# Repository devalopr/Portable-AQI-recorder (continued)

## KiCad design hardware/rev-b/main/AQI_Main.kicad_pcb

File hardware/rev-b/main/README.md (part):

# AQI main board — Rev B

Open `AQI_Main.kicad_pro` in KiCad 10. This board mates with the IP5310 battery board, which now lives in its own private repo, [18650-USB-C-UPS](https://github.com/devalopr/18650-USB-C-UPS). It started from the routed Rev A main board, whose design is kept in `review/rev-a-baseline/` as the input to `main_revb_design.py`; the rest of Rev A is in git history.

**47 × 76 mm, two layers, 1.6 mm.** This is 4 mm shorter and 3 mm wider than Rev A, and two layers instead of four. The previous 4-layer, 80 mm version is kept in `review/rev-b-4layer-80mm/` (board, `design.json` and its cost).

Changes in the 2-layer, 47 × 76 mm re-layout:

- **Wider, with mounting lips.** The board grew 1.5 mm on each long side, from 44 to 47 mm, for routing room. Board coordinates keep the Rev A origin, so the board now spans x = −1.5 to 45.5 mm. The outer 1 mm on each side (x = −1.5 to −0.5 and 44.5 to 45.5 mm) is a lip for clamping the board in the case. It carries only the ground pour: no tracks or vias. SW4 moved out 1.5 mm with the edge.

- **Shorter bottom.** Everything below the buttons moved up 4 mm and the bottom edge was cut to match:
  - the ESP32 module, which keeps its antenna at the edge, and its supply caps;
  - USB-C and D1;
  - the J2/J8 headers.

  The limit is USB-C: its shield legs pass through the board and must stay clear of the OK button's pads.
- **CO₂ on top.** The CO₂ island is now at the top of the right column (y = 21–35 mm, under J5), above SEN5x and SEN6x. It is fed through its bottom-right tab instead of the middle tab (see Layout). Set `ISLAND_DY = 0` in `main_revb_2layer.py` to go back to the island at the bottom of the column.
- **Sensor connectors.** J3 (SEN5x, y = 37–49 mm) and J4 (SEN6x, y = 49.8–59.4 mm) sit below the island, 6 mm in from the original right edge. Their mouths face the edge from x = 37.5 mm, leaving 8 mm on the board for the GH plug and for the cable to bend down before it reaches the case.
- **E-paper through an adapter.** The on-board e-paper boost circuit and its 24-pin FPC connector are gone. An unfitted 8-pin header J6 takes their place (see below).
- **Two layers.** The front copper, where only the buttons sit, carries ground plus as few signals as possible. A few critical nets are laid first as fixed routes (see Layout), and the rest are routed around them.

## Front: display and buttons

The front carries only the display and the three buttons. Everything else, including USB-C, is on the back.

- **Display.** A 2.4-inch 240 × 320 ST7789 panel with a 10-way, 1.0 mm-pitch flex.
  - **Size:** 42.72 × 60.26 × 2.5 mm, with a 36.72 × 48.96 mm active area (common datasheet values; you measured about 42.5 × 60 × 2.5 mm).
  - **Position:** centred in the Rev A display envelope, which spans x = 0.64–43.36 mm, y = 1.5–62.46 mm (board origin top-left, seen from the front). The panel itself spans y = 1.85–62.11 mm.
  - **Height:** it sits on 0.2 mm tape, so its front face is 2.7 mm above the board.
  - **Flex:** exits at the top, wraps over the top edge (about 1.5 mm past it) and runs into J5 on the back. The active area therefore sits toward the buttons, and firmware rotates the image.
  - **In the files:** the board-only footprint DS1 carries the panel's 3D model and outline. It isn't in the BOM or the placement file. The envelope is also drawn on Dwgs.User, labelled "TFT DISPLAY BODY (FRONT)".
  - The active-area offsets (3.0 mm at the sides, 3.2 mm at the far end, 8.1 mm at the flex end) and the flex path are typical values, not from your panel's drawing. Check them against the part you buy.
  - Nothing is placed on the front under the panel.
- **Buttons.** SW1 LEFT, SW2 OK and SW3 RIGHT sit in one row directly below the display:
  - centres at x = 9, 22 and 35 mm, y = 66.25 mm;
  - an even 13 mm pitch, centred on the board and the display (x = 22);
  - XKB TS-1187A: 5.1 × 5.1 mm body, 1.5 mm tall;
  - bodies at y = 63.7–68.8 mm, about 1.2 mm below the display edge.

  The switch tops (1.5 mm) are 1.2 mm below the display face (2.7 mm), so the enclosure needs button caps or plungers that reach the front face. The silkscreen labels L / OK / R are under each button.
- **3D models.** They are all in `lib/3d/` and the footprints point at them through `${KIPRJMOD}`; see `lib/3d/README.md`.
  - USB-C uses the LCSC catalogue model shared with the battery board.
  - KiCad 10 has no models for the TS-1187A buttons or the MSK12C02 power switch. They use simplified envelopes built from the footprint and datasheet dimensions, with their build123d sources alongside.

## Cost

About **$4.63 (₹444) per board at 1000** boards:

| At 1000 boards | Per board |
|---|---:|
| Parts | $4.01 |
| 2-layer fabrication, 47 × 76 mm | $0.13 (4-layer, 80 mm was $0.30) |
| JLC assembly | $0.49 |

Five prototypes cost about $31 each, mostly JLC's per-order assembly setup; the bare 2-layer boards are about $2 for five. Details, assumptions and exclusions are in [review/COST.md](review/COST.md). Only the SCD41 (U8) and the J6/J8 headers are unfitted; the CO₂ supply (LDO U7 with C15, C16 and C42, about $0.24) is assembled so the sensor can be soldered in later on its own. The same design with its original parts was about $10.7 (₹1030) at 1000.

## E-paper option (J6, unfitted)

The stationary version can use an e-paper display instead of the TFT. The panel from the Rev A brief, Good Display GDEY037T03, is a bare panel: it needs a boost circuit (about ±15 V gate and source rails) on whatever board its 24-pin flex plugs into. Rev A put that circuit on this board as an unfitted option: 22 parts plus the FPC connector. Rev B leaves the boost circuit to an external adapter instead:

- **Adapter.** Good Display's DESPI-C02 takes the panel's 24-pin flex and makes the rails. The same adapter fits most of Good Display's 24-pin SPI panels, so the main board isn't tied to one panel. A module with its own driver board (for example Waveshare's) also works.
- **J6.** A 1 × 8, 2.54 mm SMD pin header on the back at the top-left edge (pads staggered at x = 3.35 and 6.66 mm, y = 1.5–19.3 mm). Like J8, it is unfitted (DNP) by default and is left out of the JLC BOM and placement files; solder it by hand for an e-paper build. It sits near the board edge, clear of J5, so there's room for the iron. It's surface-mount so no through-hole pads sit under the TFT in the default build. Pin 1 is at the top; the pin names are on the back silkscreen, on the side toward J5.

| J6 pin | DESPI-C02 pin | Signal | ESP32 |
|---:|---|---|---|
| 1 | BUSY | EPD_BUSY | GPIO20 |
| 2 | RES | DISP_RST | GPIO7 |
| 3 | D/C | DISP_DC | GPIO10 |
| 4 | CS | DISP_CS | GPIO4 |
| 5 | SCK | DISP_SCK | GPIO5 |
| 6 | SDI | DISP_MOSI | GPIO6 |
| 7 | GND | GND | |
| 8 | 3.3V | +3V2 (3.19 V) | |

A straight 8-way female-to-female cable maps J6 pin n to DESPI-C02 pin n. Waveshare modules use the same signals in reverse order (VCC, GND, DIN, CLK, CS, DC, RST, BUSY).

The display SPI, CS, DC and reset are shared with the TFT, so **fit one display only**. The adapter's supply comes from the +3V2 rail; e-paper refresh current is small. Firmware still has to supply a driver for the chosen panel: ESPHome has no working UC8253 (GDEY037T03) driver yet (see the Rev A brief), so either pick a panel ESPHome supports or bench-test a custom component.

## Interface to the battery board

- **USB-C J1 is the only power and data input.** It is the same SHOU HAN TYPE-C 16P L6.5 (LCSC C49287211) as the battery board's J1 and J7, using that board's footprint (checked against the maker's drawing) and 3D model. It is on the back, at x = 26.7 mm on the bottom edge (y = 76), with its mouth flush with the edge. That is about 11 mm nearer the centre than in Rev A. Plug it into the battery board's USB-C output J7, which carries 5 V plus USB data passed through from the battery board's input port. It can also plug straight into a computer or adapter.
- **J2: straight 2.54 mm Dupont header for battery %** (hanxia HX PZ2.54-1x2P ZZ, LCSC C32713268), back side, bottom-right, pin 1 at (33.85, 72.1) mm. The pins stand up from the back, toward the battery board; nothing overhangs the edge. Pin 1 = GND, pin 2 = BAT_PWM, the same order as battery J9, so a straight female-female jumper works. R33 (10 kΩ) pulls BAT_PWM up to +3V2; R34 (1 kΩ) feeds GPIO21. Encoding and receiver: `../firmware/telemetry/README.md`.
- **J8: straight Dupont header for external 5 V, unpopulated** (same part), next to J2 (pin 1 at x = 39.95 mm). Pin 1 = GND, pin 2 = 5 V in. D2 (B5819W Schottky, fitted) feeds +5V_SYS, the same point as USB VBUS. The switch and regulators work as normal, and the diode stops the board back-feeding the external supply. A supply above USB VBUS + 0.3 V can back-feed a connected USB host, so don't plug USB into a computer while an external 5 V is attached.
- Removed with the 10-way JST GH link:
  - the TS3USB30E USB data mux;
  - the TPS2116 power mux;
  - their FETs and resistors;
  - C4, C5, C6 and R24.

  No I2C runs to the battery board any more.

## Cost-down changes (same functions)

| Part | Rev A | Rev B |
|---|---|---|
| U5, U6 bucks | TPS62160 (MSOP-8) | Silergy SY8089A1AAC (SOT-23-5). The datasheet's optional feed-forward caps are omitted. |
| Buttons | MCP23008 I2C expander + C&K KMR2 | Straight to GPIOs; XKB TS-1187A 5.1 mm switches. U9, C17, R23 and R25 removed. |
| Backlight | STCS05A current sink (not stocked at JLC) | AO3400A low-side switch Q1 with R28 = 33 Ω 1206 (~55 mA at Vf 3.1 V). Still PWM-dimmable on GPIO3; the current is set by the resistor, not regulated. |
| Power switch | C&K JS102011SAQN | Shou Han MSK12C02; its actuator sticks out about 1.1 mm past the right edge. |
| USB-C | GCT USB4105 | SHOU HAN TYPE-C 16P L6.5, the battery board's part ($0.047 at 1000, against $0.103 for the HRO TYPE-C-31-M-12 it replaced) |
| Sensor connectors J3, J4 | JST GH | XYECO GH-compatible clones, same footprint |
| ESD, MCU | ST USBLC6-2SC6, ESP32-C3-MINI-1-H4 | Tech Public USBLC6-2SC6, ESP32-C3-MINI-1-H4X (same footprint) |

Every fitted part has an LCSC code in the schematic. `review/jlc-bom.csv` and `review/jlc-cpl.csv` are ready for JLCPCB assembly. The board is double-sided: the three buttons are on the front and everything else is on the back.

The TFT connector (TE 1-84953-0, $0.44) stays: no cheap top-contact 1.0 mm 10-pin FPC connector is stocked, and the display needs top contact.

## Firmware pin map

The firmware in [firmware/](../../../firmware/README.md) uses this map. The board is programmed and logs over J1 (native USB); see that README.

| ESP32 GPIO | Function |
|---|---|
| 10 | Display DC |
| 4 | Display CS |
| 5 | Display SCK |
| 6 | Display MOSI |
| 7 | Display RST |
| 8 | LEFT button, active low, R3 pull-up |
| 9 | OK button, active low, R2 pull-up. Hold OK while resetting to enter the ROM bootloader. |
| 2 | RIGHT button, active low, R4 pull-up |
| 21 | BAT_PWM input through R34. Use native USB for logs; do not enable UART TX on GPIO21. |
| 3 | Backlight PWM, now driving a MOSFET gate (R27 pull-down) |
| 0 | I²C SDA (SEN5x at 0x69, SEN6x at 0x6B, SCD4x at 0x62) |
| 1 | I²C SCL |
| 20 | E-paper BUSY (J6 pin 1), input; also the ROM UART RX |
| 18, 19 | Native USB D−, D+ (to J1 through R7/R8 and D1) |

GPIO2, 8 and 9 are boot-strap pins. Don't hold LEFT or RIGHT while resetting; OK held at reset is the intended download mode. The buttons need a pull-up at reset, which R2–R4 provide; there's no I2C expander any more.

The 2-layer layout changed the display pins so they leave the module in the TFT connector's order (DC, CS, SCK, MOSI, RST); this lets the bus run without crossings:

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
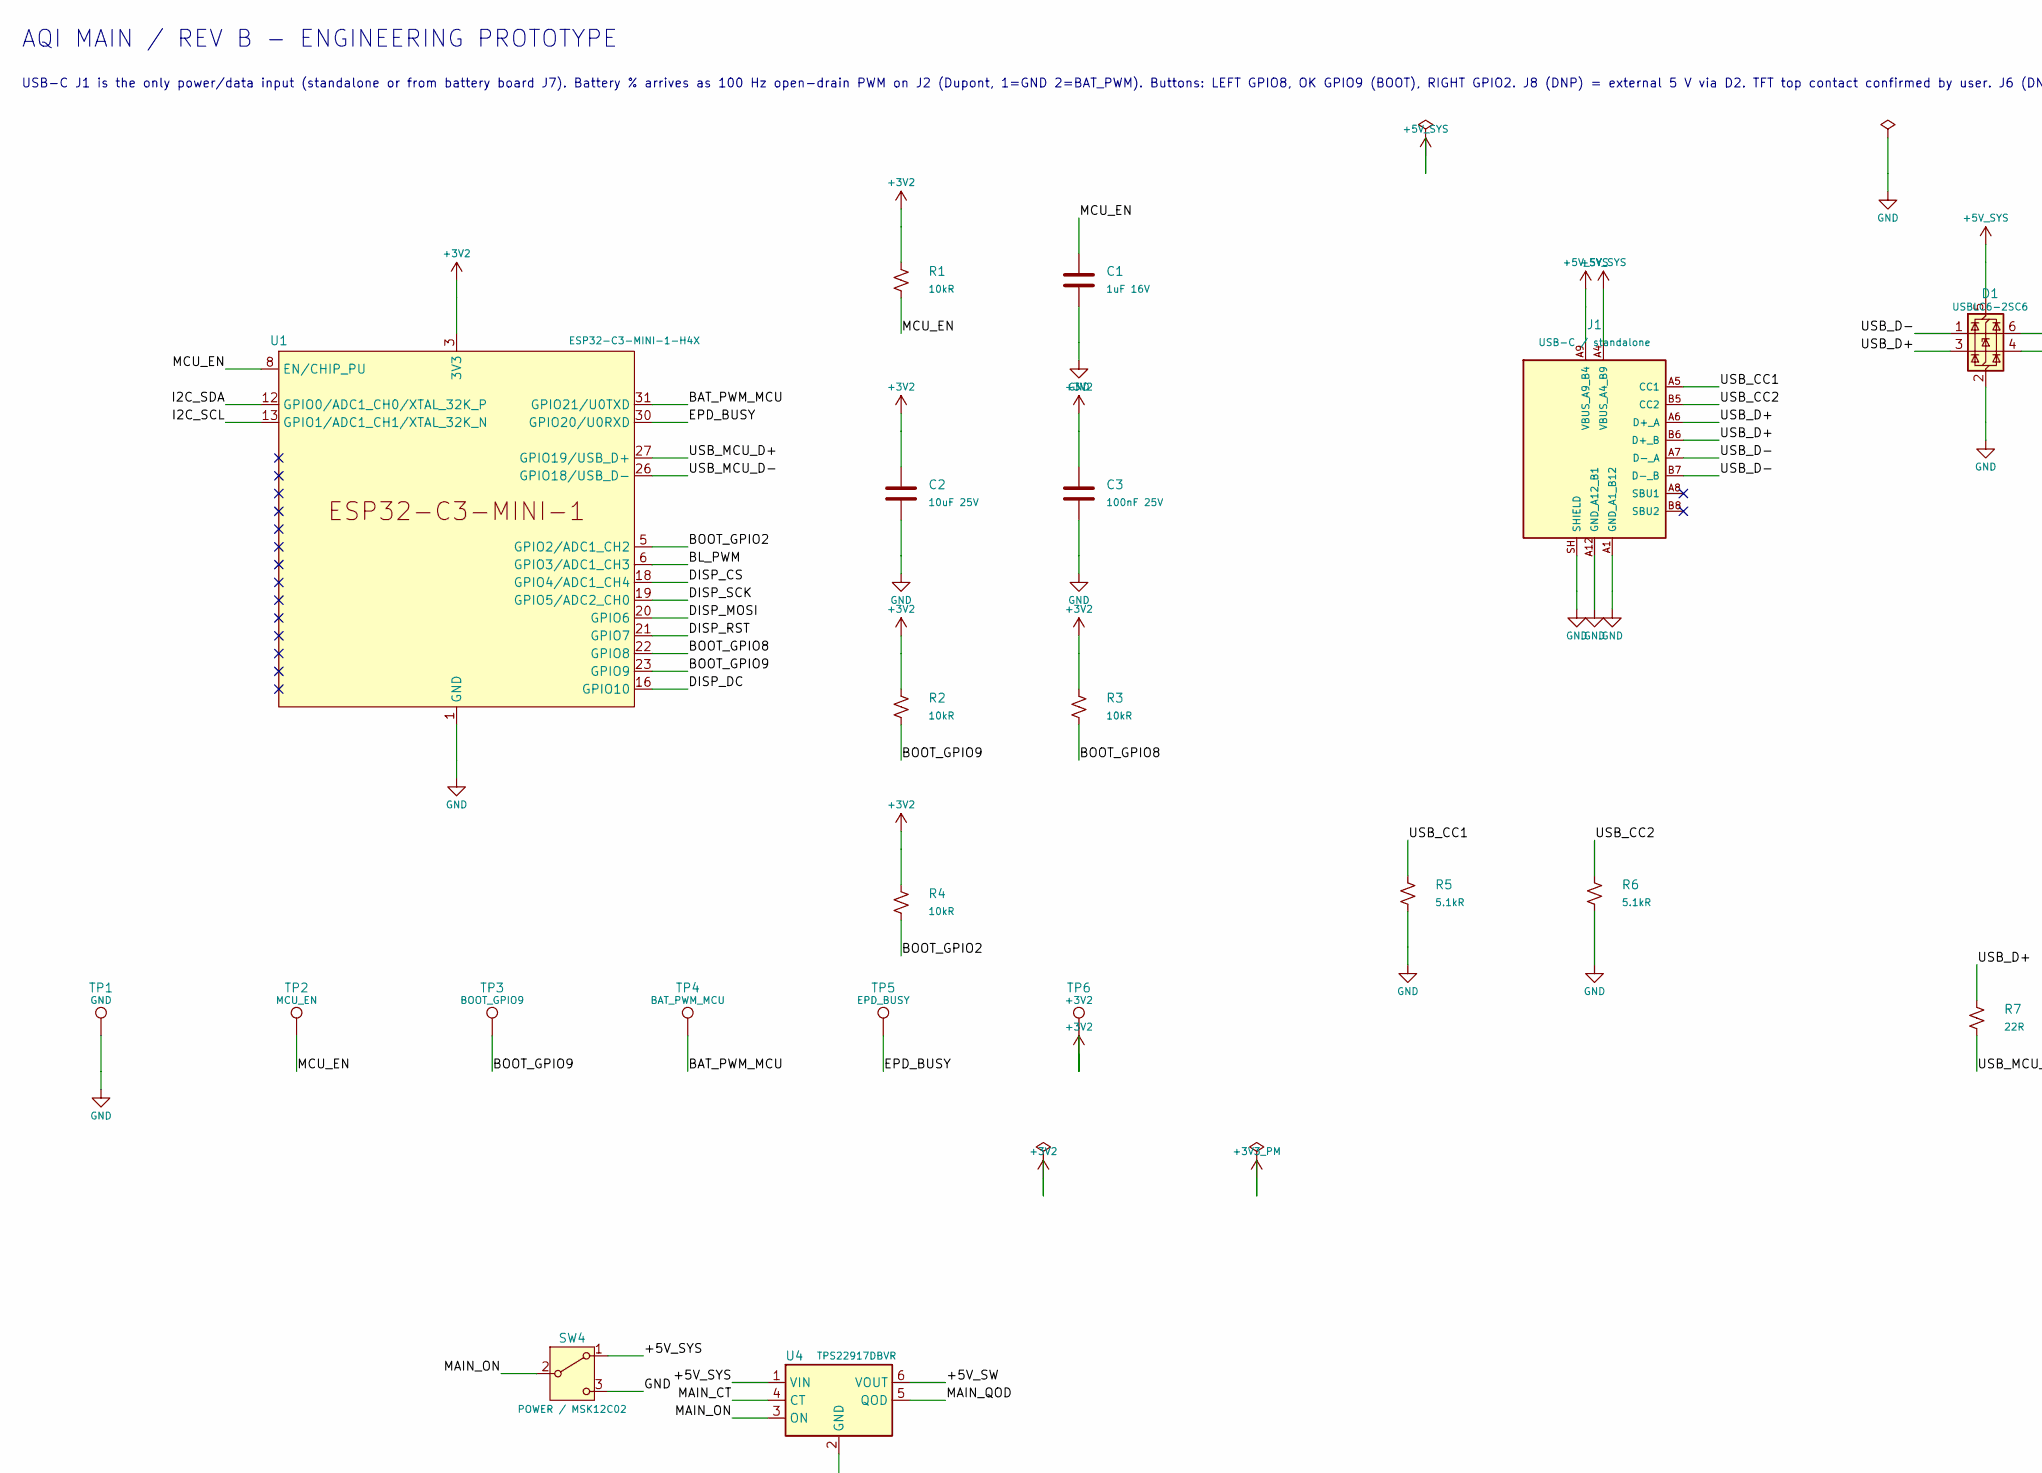
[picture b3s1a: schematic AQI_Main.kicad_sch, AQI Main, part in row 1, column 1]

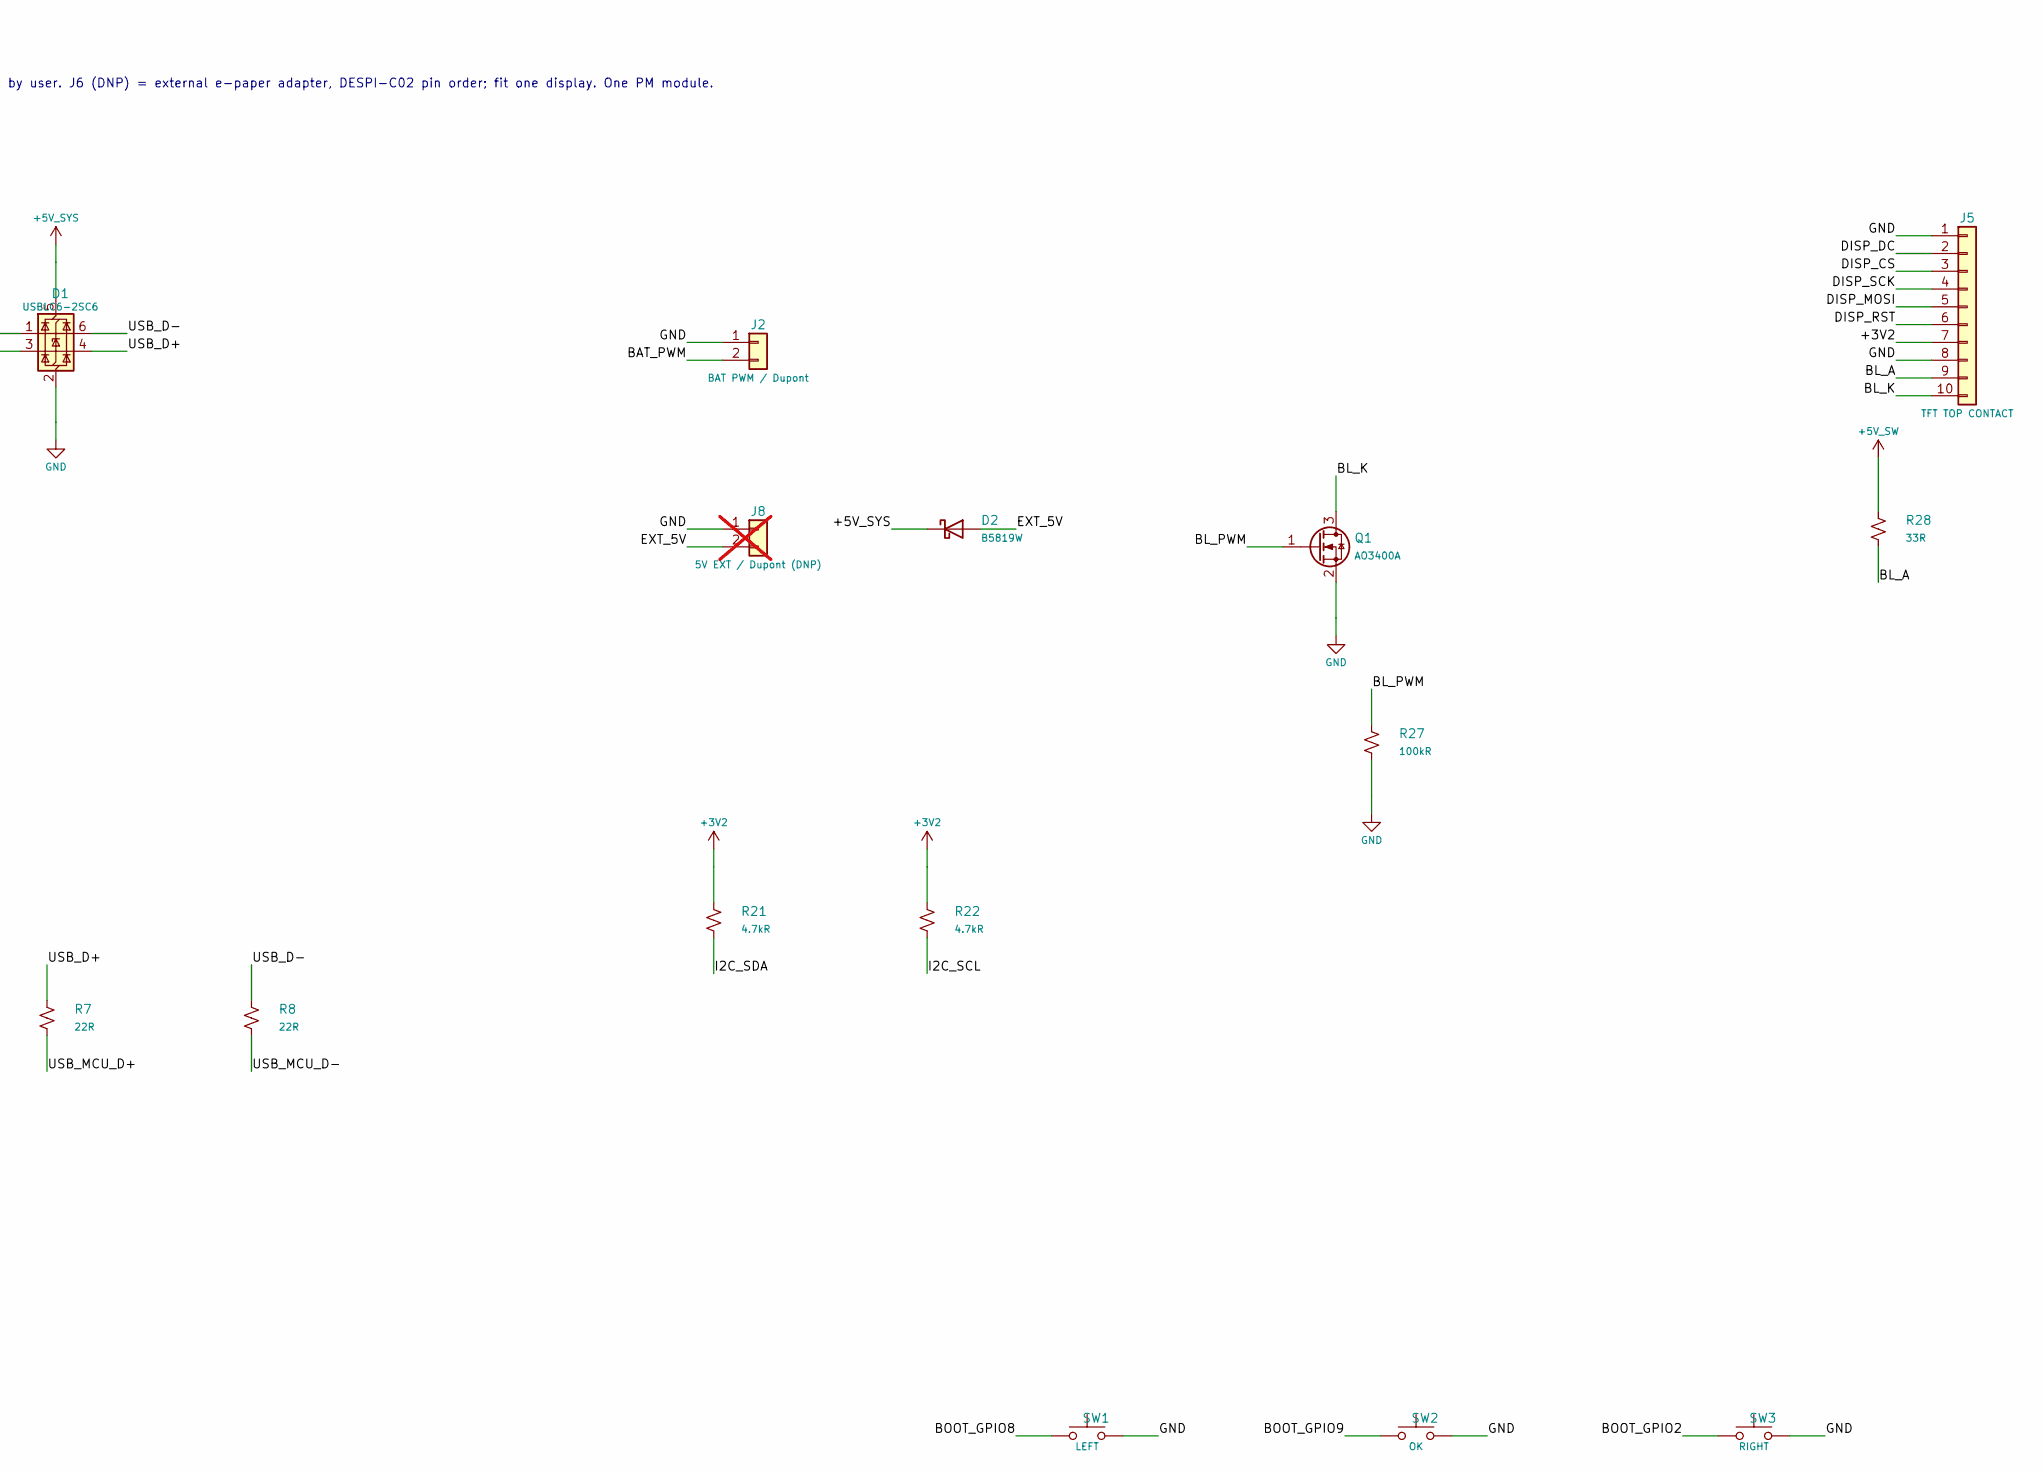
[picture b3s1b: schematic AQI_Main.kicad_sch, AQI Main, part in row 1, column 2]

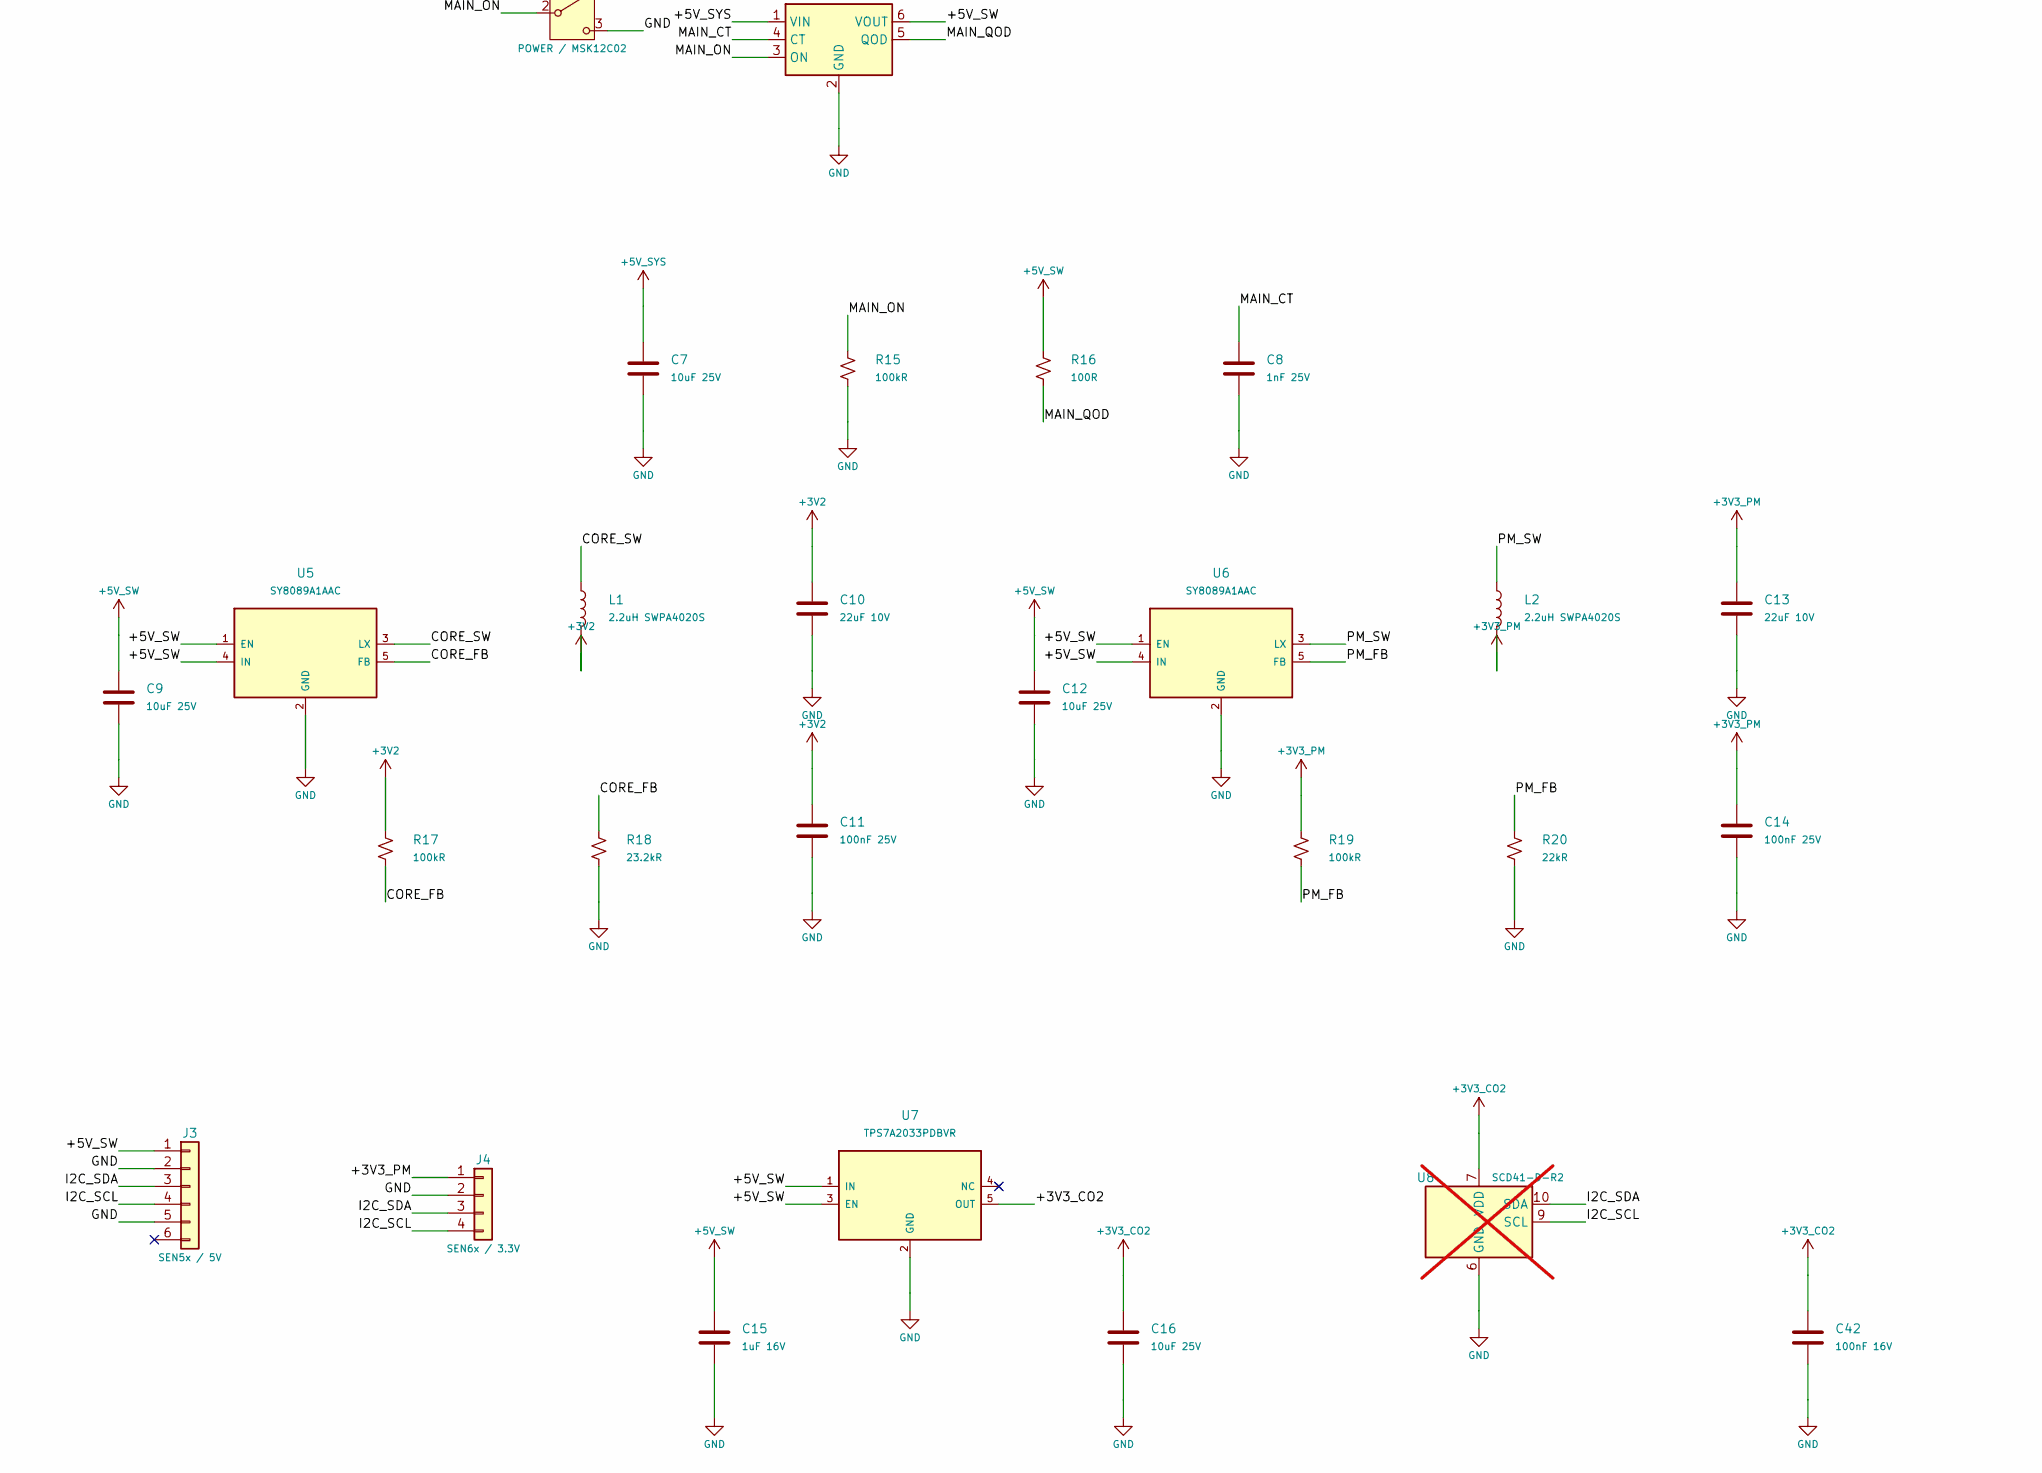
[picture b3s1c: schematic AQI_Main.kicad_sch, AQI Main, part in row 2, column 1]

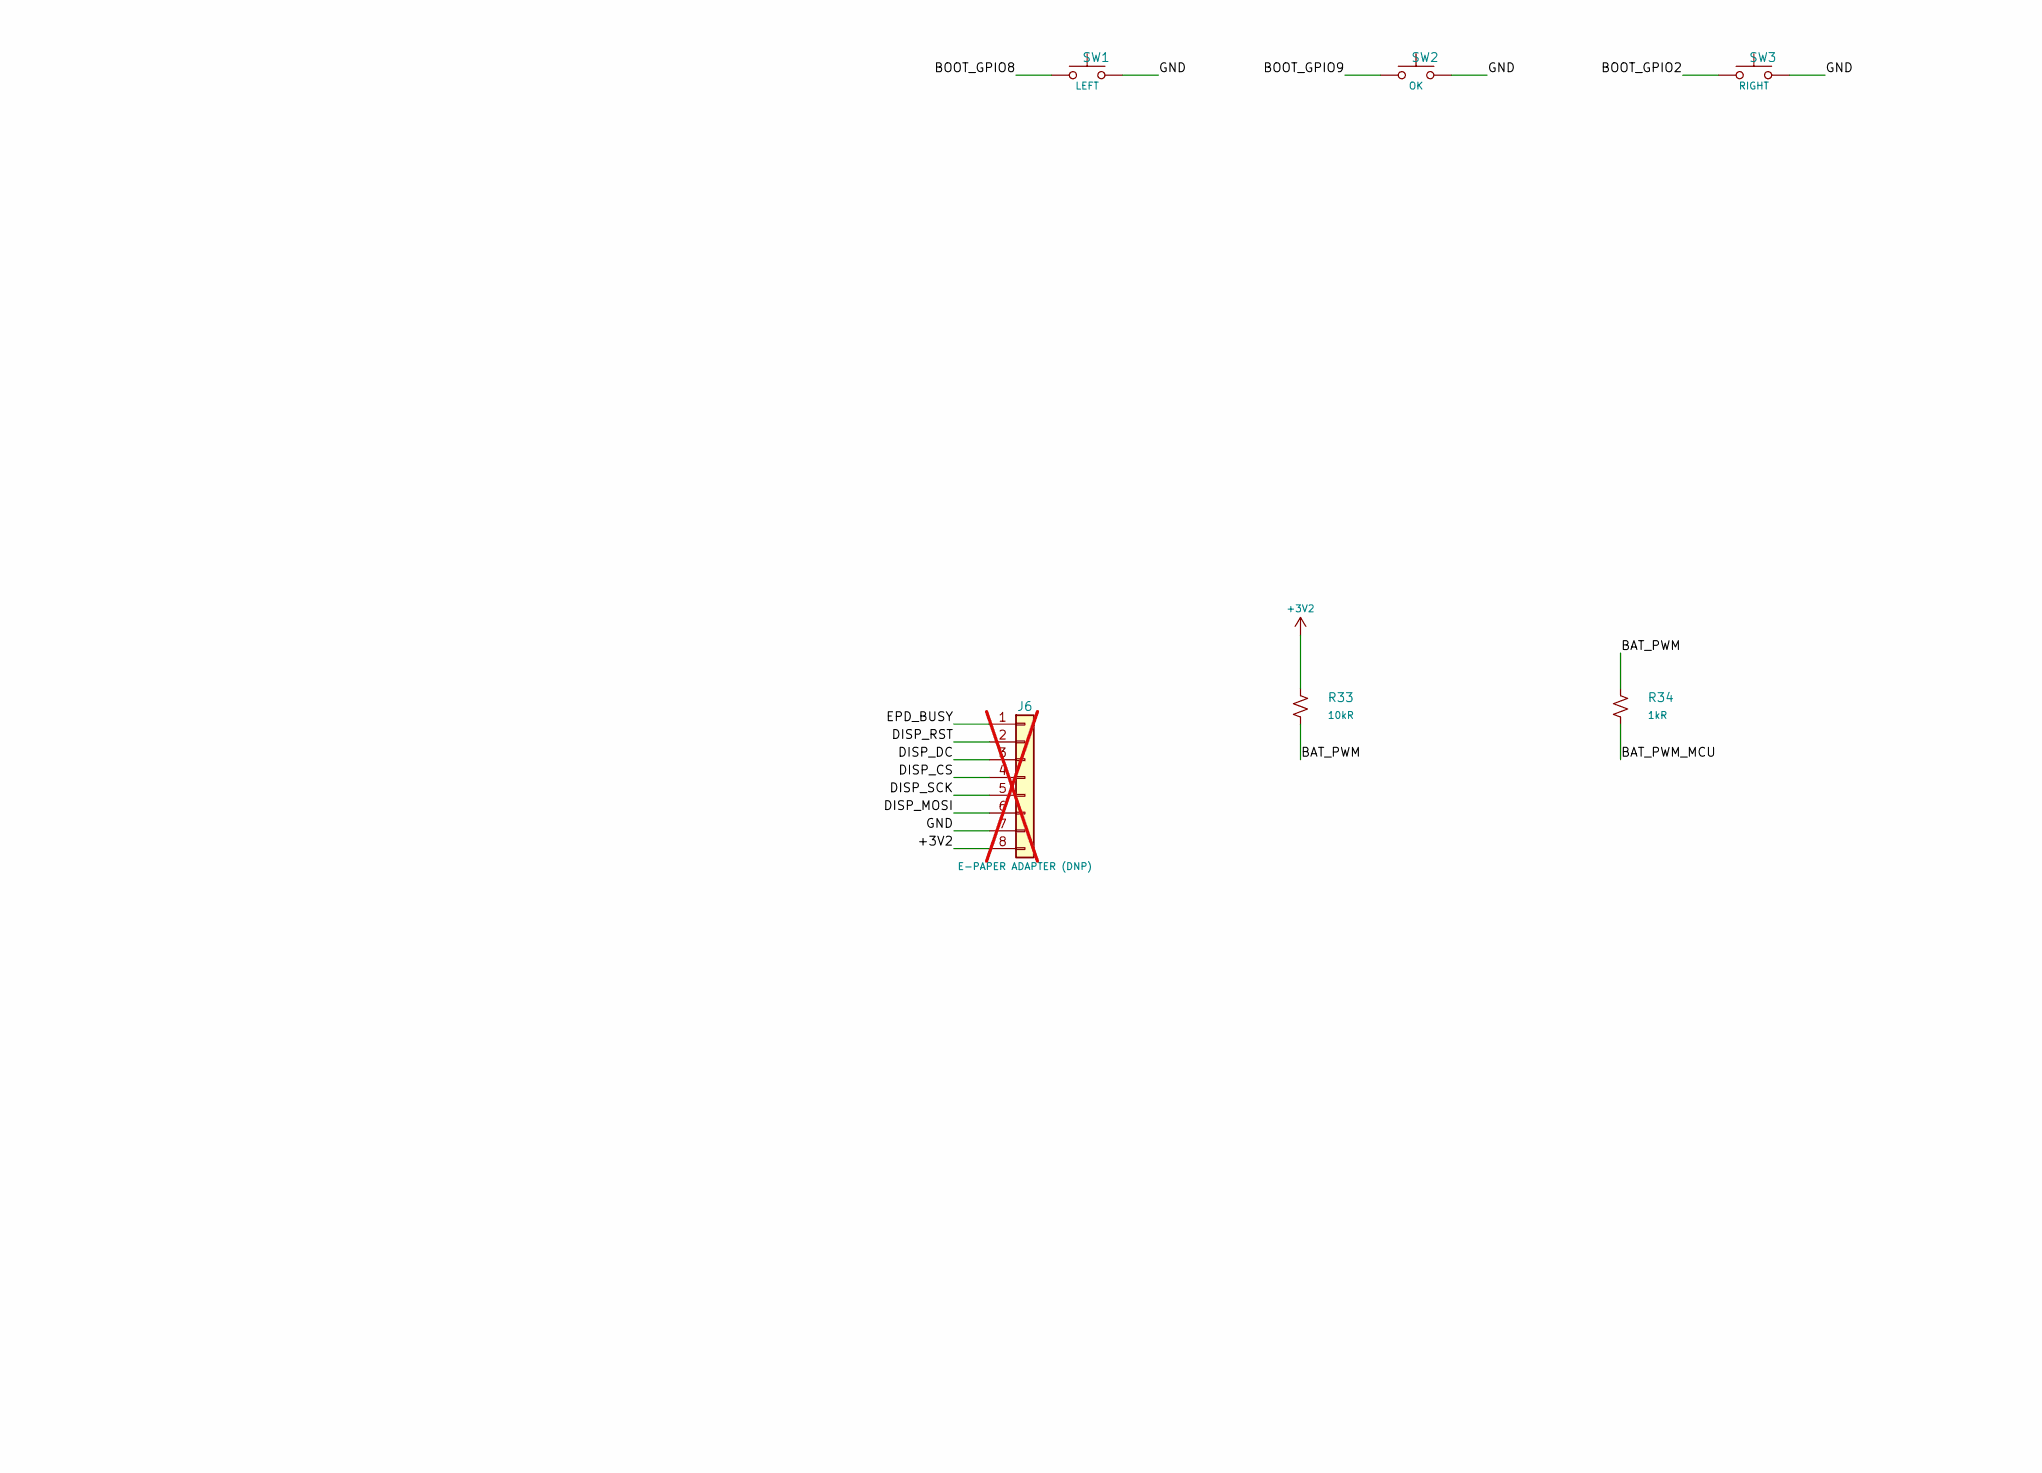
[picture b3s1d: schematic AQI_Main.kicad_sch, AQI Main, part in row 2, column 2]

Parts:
C1, C15: 1uF 16V; C_0603_1608Metric; LCSC C15849
C2, C7, C9, C12, C16: 10uF 25V; C_0805_2012Metric; LCSC C15850
C3, C11, C14: 100nF 25V; C_0603_1608Metric; LCSC C14663
C8: 1nF 25V; C_0603_1608Metric; LCSC C1588
C10, C13: 22uF 10V; C_0805_2012Metric; LCSC C45783
C42: 100nF 16V; C_0402_1005Metric; LCSC C1525
D1: USBLC6-2SC6; SOT-23-6; MPN USBLC6-2SC6; LCSC C2827654
D2: B5819W; D_SOD-123; MPN B5819W SL; LCSC C8598
J1: USB-C / standalone; USB-C-SMD_TYPE-C-16P-L6.5; MPN TYPE-C 16P L6.5; LCSC C49287211
J2: BAT PWM / Dupont; PinHeader_1x02_P2.54mm_Vertical; MPN HX PZ2.54-1x2P ZZ; LCSC C32713268
J3: SEN5x / 5V; JST_GH_SM06B-GHS-TB_1x06-1MP_P1.25mm_Horizontal; MPN XY-SM06B-GHS-TB; LCSC C51940119
J4: SEN6x / 3.3V; JST_GH_SM04B-GHS-TB_1x04-1MP_P1.25mm_Horizontal; MPN XY-SM04B-GHS-TB; LCSC C51940118
J5: TFT TOP CONTACT; TE_1-84953-0_1x10-1MP_P1.0mm_Horizontal; MPN 1-84953-0; LCSC C3168738
J6: E-PAPER ADAPTER (DNP); PinHeader_1x08_P2.54mm_Vertical_SMD_Pin1Left; MPN 2.54mm 1x08 SMD pin header; not fitted
J8: 5V EXT / Dupont (DNP); PinHeader_1x02_P2.54mm_Vertical; MPN HX PZ2.54-1x2P ZZ; LCSC C32713268; not fitted
L1, L2: 2.2uH SWPA4020S; L_Sunlord_SWPA4020S; MPN SWPA4020S2R2MT; LCSC C83423
Q1: AO3400A; SOT-23; MPN AO3400A; LCSC C20917
R1, R2, R3, R4, R33: 10kR; R_0603_1608Metric; LCSC C25804
R5, R6: 5.1kR; R_0603_1608Metric; LCSC C23186
R7, R8: 22R; R_0603_1608Metric; LCSC C23345
R15, R17, R19, R27: 100kR; R_0603_1608Metric; LCSC C25803
R16: 100R; R_0603_1608Metric; LCSC C22775
R18: 23.2kR; R_0603_1608Metric; LCSC C49656146
R20: 22kR; R_0603_1608Metric; LCSC C31850
R21, R22: 4.7kR; R_0603_1608Metric; LCSC C23162
R28: 33R; R_1206_3216Metric; LCSC C25375
R34: 1kR; R_0603_1608Metric; LCSC C21190
SW1: LEFT; SW_Push_1P1T_XKB_TS-1187A; MPN TS-1187A-B-A-B; LCSC C318884
SW2: OK; SW_Push_1P1T_XKB_TS-1187A; MPN TS-1187A-B-A-B; LCSC C318884
SW3: RIGHT; SW_Push_1P1T_XKB_TS-1187A; MPN TS-1187A-B-A-B; LCSC C318884
SW4: POWER / MSK12C02; SW_SPDT_Shouhan_MSK12C02; MPN MSK12C02; LCSC C431540
TP1: GND; TestPoint_Pad_D1.0mm
TP2: MCU_EN; TestPoint_Pad_D1.0mm
TP3: BOOT_GPIO9; TestPoint_Pad_D1.0mm
TP4: BAT_PWM_MCU; TestPoint_Pad_D1.0mm
TP5: EPD_BUSY; TestPoint_Pad_D1.0mm
TP6: +3V2; TestPoint_Pad_D1.0mm
U1: ESP32-C3-MINI-1-H4X; ESP32-C3-MINI-1; MPN ESP32-C3-MINI-1-H4X; LCSC C41349510
U4: TPS22917DBVR; SOT-23-6; MPN TPS22917DBVR; LCSC C2681320
U5, U6: SY8089A1AAC; SOT-23-5; MPN SY8089A1AAC; LCSC C479074
U7: TPS7A2033PDBVR; SOT-23-5; MPN TPS7A2033PDBVR; LCSC C2862740
U8: SCD41-D-R2; Sensirion_SCD4x-1EP_10.1x10.1mm_P1.25mm_EP4.8x4.8mm; MPN SCD41-D-R2; not fitted

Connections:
+3V2: C2.1, C3.1, C10.1, C11.1, J5.7, J6.8, L1.2, R1.1, R2.1, R3.1, R4.1, R17.1, R21.1, R22.1, R33.1, TP6.1, U1.3 (3V3)
+3V3_CO2: C16.1, C42.1, U7.5 (OUT), U8.7 (VDD), U8.19 (VDD)
+3V3_PM: C13.1, C14.1, J4.1, L2.2, R19.1
+5V_SW: C9.1, C12.1, C15.1, J3.1, R16.1, R28.1, U4.6 (VOUT), U5.1 (EN), U5.4 (IN), U6.1 (EN), U6.4 (IN), U7.1 (IN), U7.3 (EN)
+5V_SYS: C7.1, D1.5 (VBUS), D2.1 (K), J1.A4 (VBUS_A4_B9), J1.A9 (VBUS_A9_B4), SW4.1 (A), U4.1 (VIN)
/BAT_PWM: J2.2, R33.2, R34.1
/BAT_PWM_MCU: R34.2, TP4.1, U1.31 (GPIO21/U0TXD)
/BL_A: J5.9, R28.2
/BL_K: J5.10, Q1.3 (D)
/BL_PWM: Q1.1 (G), R27.1, U1.6 (GPIO3/ADC1_CH3)
/BOOT_GPIO2: R4.2, SW3.1, U1.5 (GPIO2/ADC1_CH2)
/BOOT_GPIO8: R3.2, SW1.1, U1.22 (GPIO8)
/BOOT_GPIO9: R2.2, SW2.1, TP3.1, U1.23 (GPIO9)
/CORE_FB: R17.2, R18.1, U5.5 (FB)
/CORE_SW: L1.1, U5.3 (LX)
/DISP_CS: J5.3, J6.4, U1.18 (GPIO4/ADC1_CH4)
/DISP_DC: J5.2, J6.3, U1.16 (GPIO10)
/DISP_MOSI: J5.5, J6.6, U1.20 (GPIO6)
/DISP_RST: J5.6, J6.2, U1.21 (GPIO7)
/DISP_SCK: J5.4, J6.5, U1.19 (GPIO5/ADC2_CH0)
/EPD_BUSY: J6.1, TP5.1, U1.30 (GPIO20/U0RXD)
/EXT_5V: D2.2 (A), J8.2
/I2C_SCL: J3.4, J4.4, R22.2, U1.13 (GPIO1/ADC1_CH1/XTAL_32K_N), U8.9 (SCL)
/I2C_SDA: J3.3, J4.3, R21.2, U1.12 (GPIO0/ADC1_CH0/XTAL_32K_P), U8.10 (SDA)
/MAIN_CT: C8.1, U4.4 (CT)
/MAIN_ON: R15.1, SW4.2 (B), U4.3 (ON)
/MAIN_QOD: R16.2, U4.5 (QOD)
/MCU_EN: C1.1, R1.2, TP2.1, U1.8 (EN/CHIP_PU)
/PM_FB: R19.2, R20.1, U6.5 (FB)
/PM_SW: L2.1, U6.3 (LX)
/USB_CC1: J1.A5 (CC1), R5.1
/USB_CC2: J1.B5 (CC2), R6.1
/USB_D+: D1.3 (I/O2), D1.4 (I/O2), J1.A6 (D+_A), J1.B6 (D+_B), R7.1
/USB_D-: D1.1 (I/O1), D1.6 (I/O1), J1.A7 (D-_A), J1.B7 (D-_B), R8.1
/USB_MCU_D+: R7.2, U1.27 (GPIO19/USB_D+)
/USB_MCU_D-: R8.2, U1.26 (GPIO18/USB_D-)
GND: C1.2, C2.2, C3.2, C7.2, C8.2, C9.2, C10.2, C11.2, C12.2, C13.2, C14.2, C15.2, C16.2, C42.2, D1.2 (GND), J1.A1 (GND_A1_B12), J1.A12 (GND_A12_B1), J1.SH (SHIELD), J2.1, J3.2, J3.5, J4.2, J5.1, J5.8, J6.7, J8.1, Q1.2 (S), R5.2, R6.2, R15.2, R18.2, R20.2, R27.2, SW1.2, SW2.2, SW3.2, SW4.3 (C), TP1.1, U1.1 (GND), U1.2 (GND), U1.11 (GND), U1.14 (GND), U1.36 (GND), U1.37 (GND), U1.38 (GND), U1.39 (GND), U1.40 (GND), U1.41 (GND), U1.42 (GND), U1.43 (GND), U1.44 (GND), U1.45 (GND), U1.46 (GND), U1.47 (GND), U1.48 (GND), U1.49 (GND), U1.50 (GND), U1.51 (GND), U1.52 (GND), U1.53 (GND), U4.2 (GND), U5.2 (GND), U6.2 (GND), U7.2 (GND), U8.6 (GND), U8.20 (GND), U8.21 (GND)

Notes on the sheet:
AQI MAIN / REV B - ENGINEERING PROTOTYPE
USB-C J1 is the only power/data input (standalone or from battery board J7). Battery % arrives as 100 Hz open-drain PWM on J2 (Dupont, 1=GND 2=BAT_PWM). Buttons: LEFT GPIO8, OK GPIO9 (BOOT), RIGHT GPIO2. J8 (DNP) = external 5 V via D2. TFT top contact confirmed by user. J6 (DNP) = external e-paper 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

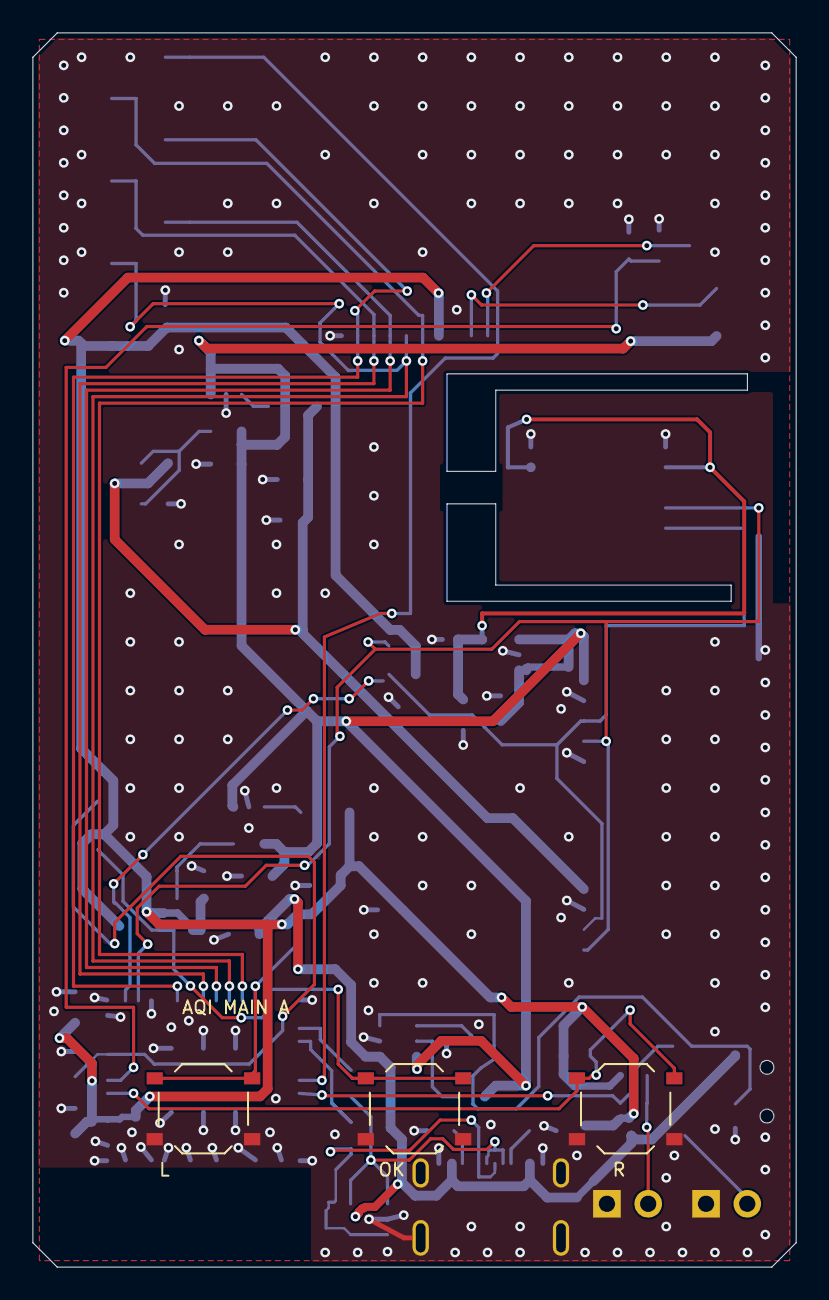
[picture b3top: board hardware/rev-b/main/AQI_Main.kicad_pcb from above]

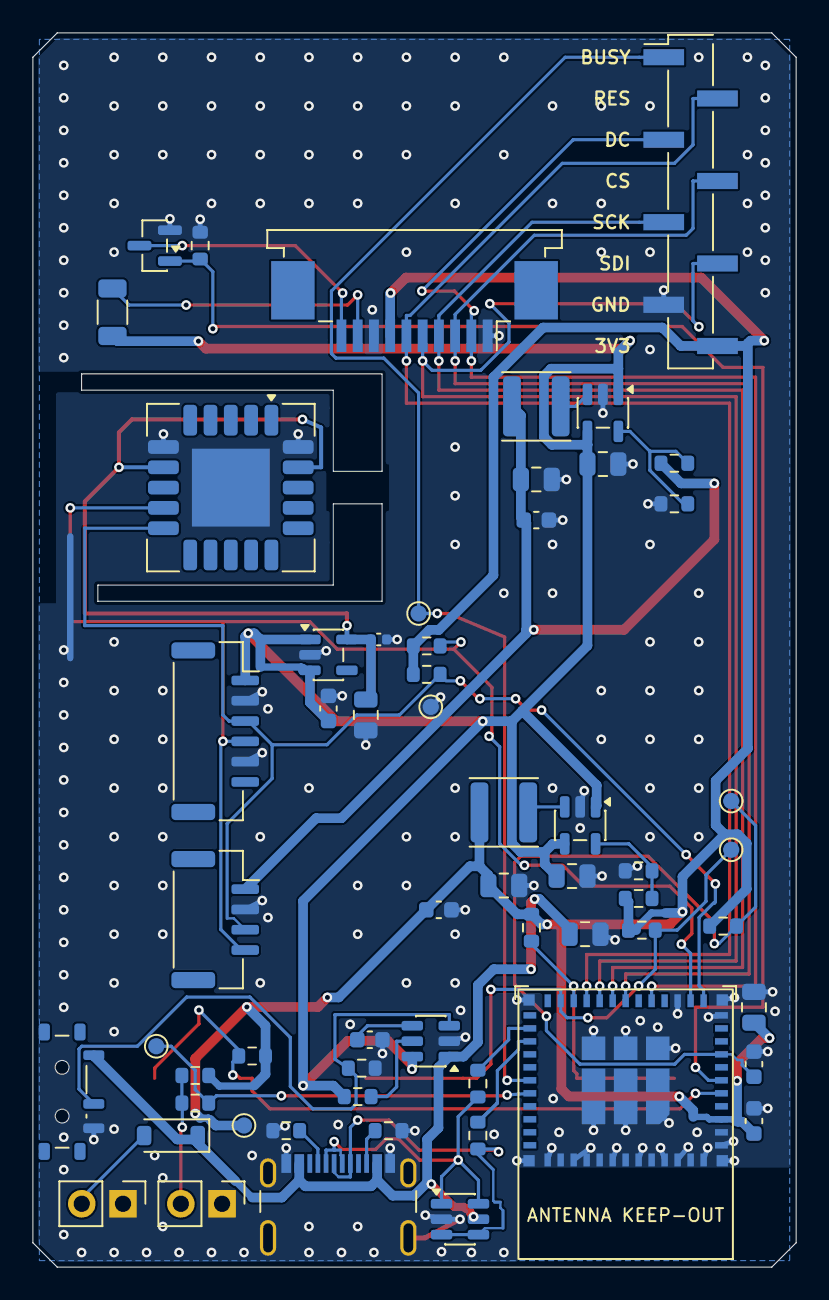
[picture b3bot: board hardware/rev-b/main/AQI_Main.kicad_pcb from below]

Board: 2 copper layers, 47.0 x 76.0 mm, 63 parts (59 on the bottom side), 37 nets.

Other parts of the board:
DS1: TFT 2.4in ST7789 (panel); TFT_2.4in_ST7789_10P_Panel

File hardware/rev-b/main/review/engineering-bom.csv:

"Refs","Value","Footprint","MPN","Manufacturer","LCSC","DNP","Qty"
"C1,C15","1uF 16V","Capacitor_SMD:C_0603_1608Metric","","","C15849","","2"
"C2,C7,C9,C12,C16","10uF 25V","Capacitor_SMD:C_0805_2012Metric","","","C15850","","5"
"C3,C11,C14","100nF 25V","Capacitor_SMD:C_0603_1608Metric","","","C14663","","3"
"C8","1nF 25V","Capacitor_SMD:C_0603_1608Metric","","","C1588","","1"
"C10,C13","22uF 10V","Capacitor_SMD:C_0805_2012Metric","","","C45783","","2"
"C42","100nF 16V","Capacitor_SMD:C_0402_1005Metric","","","C1525","","1"
"D1","USBLC6-2SC6","Package_TO_SOT_SMD:SOT-23-6","USBLC6-2SC6","TECH PUBLIC","C2827654","","1"
"D2","B5819W","Diode_SMD:D_SOD-123","B5819W SL","Changjiang","C8598","","1"
"J1","USB-C / standalone","AQI:USB-C-SMD_TYPE-C-16P-L6.5","TYPE-C 16P L6.5","SHOU HAN","C49287211","","1"
"J2","BAT PWM / Dupont","Connector_PinHeader_2.54mm:PinHeader_1x02_P2.54mm_Vertical","HX PZ2.54-1x2P ZZ","hanxia","C32713268","","1"
"J3","SEN5x / 5V","Connector_JST:JST_GH_SM06B-GHS-TB_1x06-1MP_P1.25mm_Horizontal","XY-SM06B-GHS-TB","XYECO","C51940119","","1"
"J4","SEN6x / 3.3V","Connector_JST:JST_GH_SM04B-GHS-TB_1x04-1MP_P1.25mm_Horizontal","XY-SM04B-GHS-TB","XYECO","C51940118","","1"
"J5","TFT TOP CONTACT","Connector_FFC-FPC:TE_1-84953-0_1x10-1MP_P1.0mm_Horizontal","1-84953-0","TE Connectivity","C3168738","","1"
"J6","E-PAPER ADAPTER (DNP)","Connector_PinHeader_2.54mm:PinHeader_1x08_P2.54mm_Vertical_SMD_Pin1Left","2.54mm 1x08 SMD pin header","","","DNP","1"
"J8","5V EXT / Dupont (DNP)","Connector_PinHeader_2.54mm:PinHeader_1x02_P2.54mm_Vertical","HX PZ2.54-1x2P ZZ","hanxia","C32713268","DNP","1"
"L1,L2","2.2uH SWPA4020S","Inductor_SMD:L_Sunlord_SWPA4020S","SWPA4020S2R2MT","Sunlord","C83423","","2"
"Q1","AO3400A","Package_TO_SOT_SMD:SOT-23","AO3400A","Alpha & Omega","C20917","","1"
"R1-R4,R33","10kR","Resistor_SMD:R_0603_1608Metric","","","C25804","","5"
"R5,R6","5.1kR","Resistor_SMD:R_0603_1608Metric","","","C23186","","2"
"R7,R8","22R","Resistor_SMD:R_0603_1608Metric","","","C23345","","2"
"R15,R17,R19,R27","100kR","Resistor_SMD:R_0603_1608Metric","","","C25803","","4"
"R16","100R","Resistor_SMD:R_0603_1608Metric","","","C22775","","1"
"R18","23.2kR","Resistor_SMD:R_0603_1608Metric","","","C49656146","","1"
"R20","22kR","Resistor_SMD:R_0603_1608Metric","","","C31850","","1"
"R21,R22","4.7kR","Resistor_SMD:R_0603_1608Metric","","","C23162","","2"
"R28","33R","Resistor_SMD:R_1206_3216Metric","","","C25375","","1"
"R34","1kR","Resistor_SMD:R_0603_1608Metric","","","C21190","","1"
"SW1","LEFT","Button_Switch_SMD:SW_Push_1P1T_XKB_TS-1187A","TS-1187A-B-A-B","XKB","C318884","","1"
"SW2","OK","Button_Switch_SMD:SW_Push_1P1T_XKB_TS-1187A","TS-1187A-B-A-B","XKB","C318884","","1"
"SW3","RIGHT","Button_Switch_SMD:SW_Push_1P1T_XKB_TS-1187A","TS-1187A-B-A-B","XKB","C318884","","1"
"SW4","POWER / MSK12C02","Button_Switch_SMD:SW_SPDT_Shouhan_MSK12C02","MSK12C02","SHOU HAN","C431540","","1"
"TP1","GND","TestPoint:TestPoint_Pad_D1.0mm","","","","","1"
"TP2","MCU_EN","TestPoint:TestPoint_Pad_D1.0mm","","","","","1"
"TP3","BOOT_GPIO9","TestPoint:TestPoint_Pad_D1.0mm","","","","","1"
"TP4","BAT_PWM_MCU","TestPoint:TestPoint_Pad_D1.0mm","","","","","1"
"TP5","EPD_BUSY","TestPoint:TestPoint_Pad_D1.0mm","","","","","1"
"TP6","+3V2","TestPoint:TestPoint_Pad_D1.0mm","","","","","1"
"U1","ESP32-C3-MINI-1-H4X","AQI:ESP32-C3-MINI-1","ESP32-C3-MINI-1-H4X","Espressif","C41349510","","1"
"U4","TPS22917DBVR","Package_TO_SOT_SMD:SOT-23-6","TPS22917DBVR","Texas Instruments","C2681320","","1"
"U5,U6","SY8089A1AAC","Package_TO_SOT_SMD:SOT-23-5","SY8089A1AAC","Silergy","C479074","","2"
"U7","TPS7A2033PDBVR","Package_TO_SOT_SMD:SOT-23-5","TPS7A2033PDBVR","Texas Instruments","C2862740","","1"
"U8","SCD41-D-R2","Sensor:Sensirion_SCD4x-1EP_10.1x10.1mm_P1.25mm_EP4.8x4.8mm","SCD41-D-R2","Sensirion","","DNP","1"
